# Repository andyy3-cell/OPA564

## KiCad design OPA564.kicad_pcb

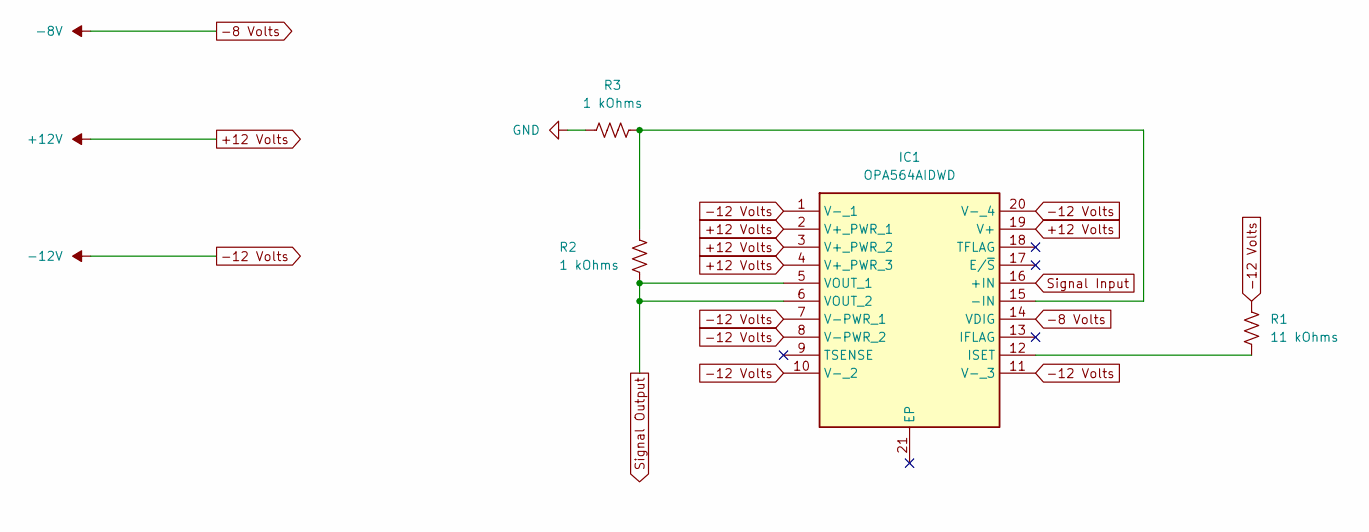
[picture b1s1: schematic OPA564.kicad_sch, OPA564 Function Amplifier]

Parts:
IC1: OPA564AIDWD; SOIC127P1040X265-21N; Mouser Part Number 595-OPA564AIDWD
R1: 11 kOhms; R_0805_2012Metric_Pad1.20x1.40mm_HandSolder
R2, R3: 1 kOhms; R_0805_2012Metric_Pad1.20x1.40mm_HandSolder

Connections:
+12 Volts: IC1.2 (V+_PWR_1), IC1.3 (V+_PWR_2), IC1.4 (V+_PWR_3), IC1.19 (V+)
-8 Volts: IC1.14 (VDIG)
-12 Volts: IC1.1 (V-_1), IC1.7 (V-PWR_1), IC1.8 (V-PWR_2), IC1.10 (V-_2), IC1.11 (V-_3), IC1.20 (V-_4), R1.1
GND: R3.1
unnamed: IC1.15 (-IN), R2.1, R3.2
unnamed: IC1.12 (ISET), R1.2
Signal Input: IC1.16 (+IN)
Signal Output: IC1.5 (VOUT_1), IC1.6 (VOUT_2), R2.2

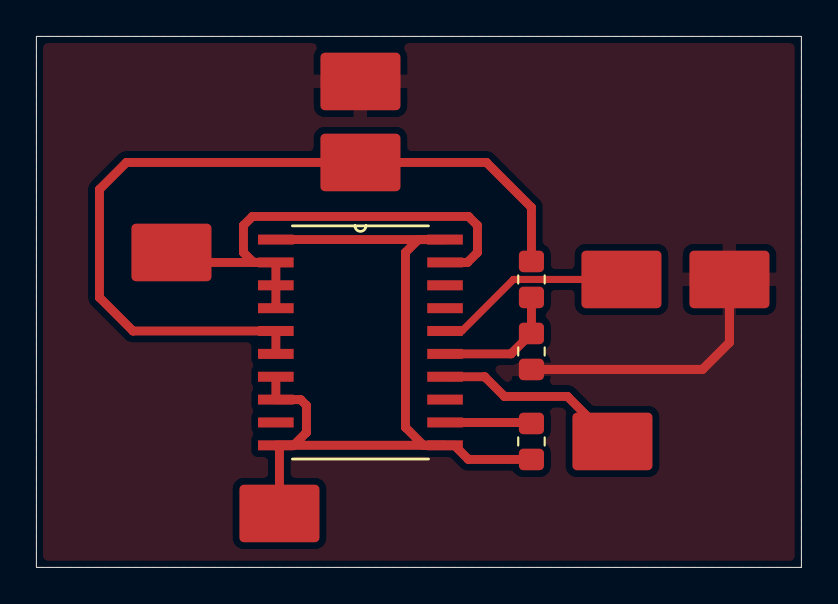
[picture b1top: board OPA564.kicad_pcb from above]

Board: 2 copper layers, 42.5 x 29.5 mm, 4 parts (0 on the bottom side), 5 nets.

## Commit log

2026-05-25 opa564
2026-05-26 finished adding all footprints i think
2026-05-26 Rough Sketch of PCB design has been finished
2026-05-28 OPA564 without Voltage Follower
2026-06-08 zone areas
2026-06-09 no real changes
2026-06-17 OPA564 simplest design
2026-06-23 OPA564 Thicker Tracks
2026-06-23 gerbers
